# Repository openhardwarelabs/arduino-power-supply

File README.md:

arduino-power-supply
====================

A simple power supply board for Arduino, that converts 110v - 230v AC voltage to 5v &amp; 3.3v DC. Perfect to power up Arduino projects &amp; other microcontrollers.

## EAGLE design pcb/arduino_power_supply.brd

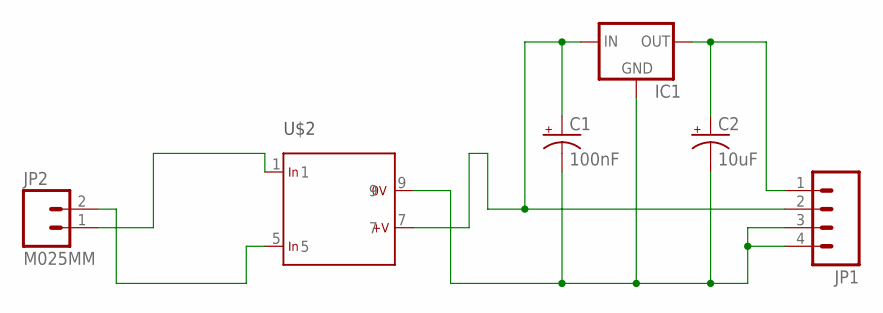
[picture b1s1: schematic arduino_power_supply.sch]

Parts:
C1: 100nF; CPOL-RADIAL-10UF-25V
C2: 10uF; CPOL-RADIAL-10UF-25V
IC1: 78XXS
JP1: M04PTH; 1X04
JP2: M025MM; SCREWTERMINAL-5MM-2
U$2: SINGLE; 1

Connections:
unnamed: C1.2 (-), C2.2 (-), IC1.GND, JP1.3, JP1.4, U$2.9
unnamed: C1.1 (+), IC1.IN, JP1.2, U$2.7
unnamed: C2.1 (+), IC1.OUT, JP1.1
unnamed: JP2.1, U$2.1
unnamed: JP2.2, U$2.5

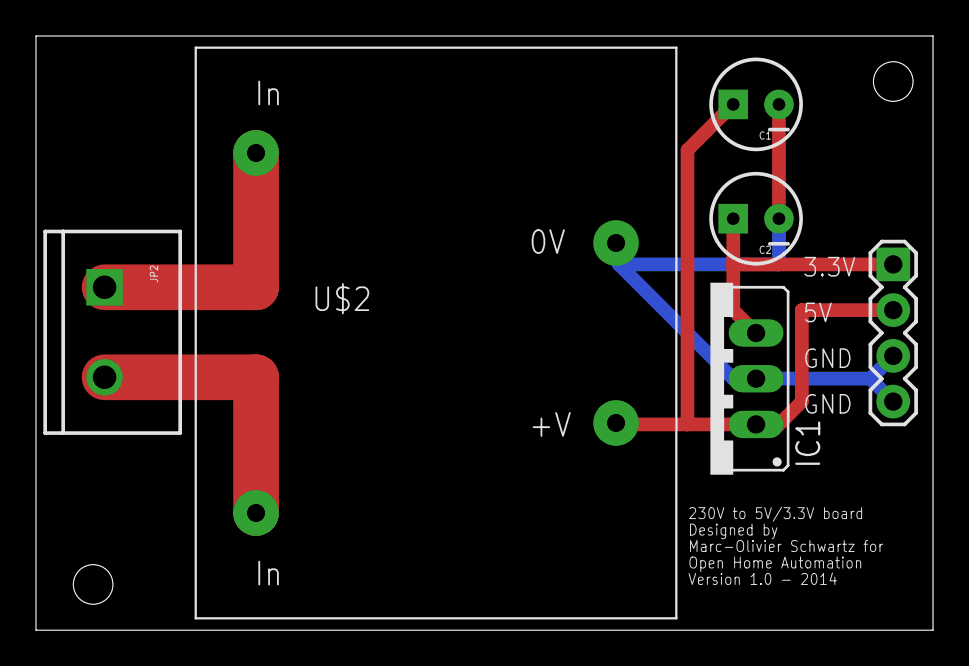
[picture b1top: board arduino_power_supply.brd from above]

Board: 2 copper layers, 49.8 x 33.0 mm, 6 parts (0 on the bottom side), 5 nets.

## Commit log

2014-07-10 added recipe
2014-07-10 added recipe and small fixes
2014-07-10 added PDF recipe

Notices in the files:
parts and their libraries:
SparkFun-Connectors: Licensing: Creative Commons ShareAlike 4.0 International - https://creativecommons.org/licenses/by-sa/4.0
